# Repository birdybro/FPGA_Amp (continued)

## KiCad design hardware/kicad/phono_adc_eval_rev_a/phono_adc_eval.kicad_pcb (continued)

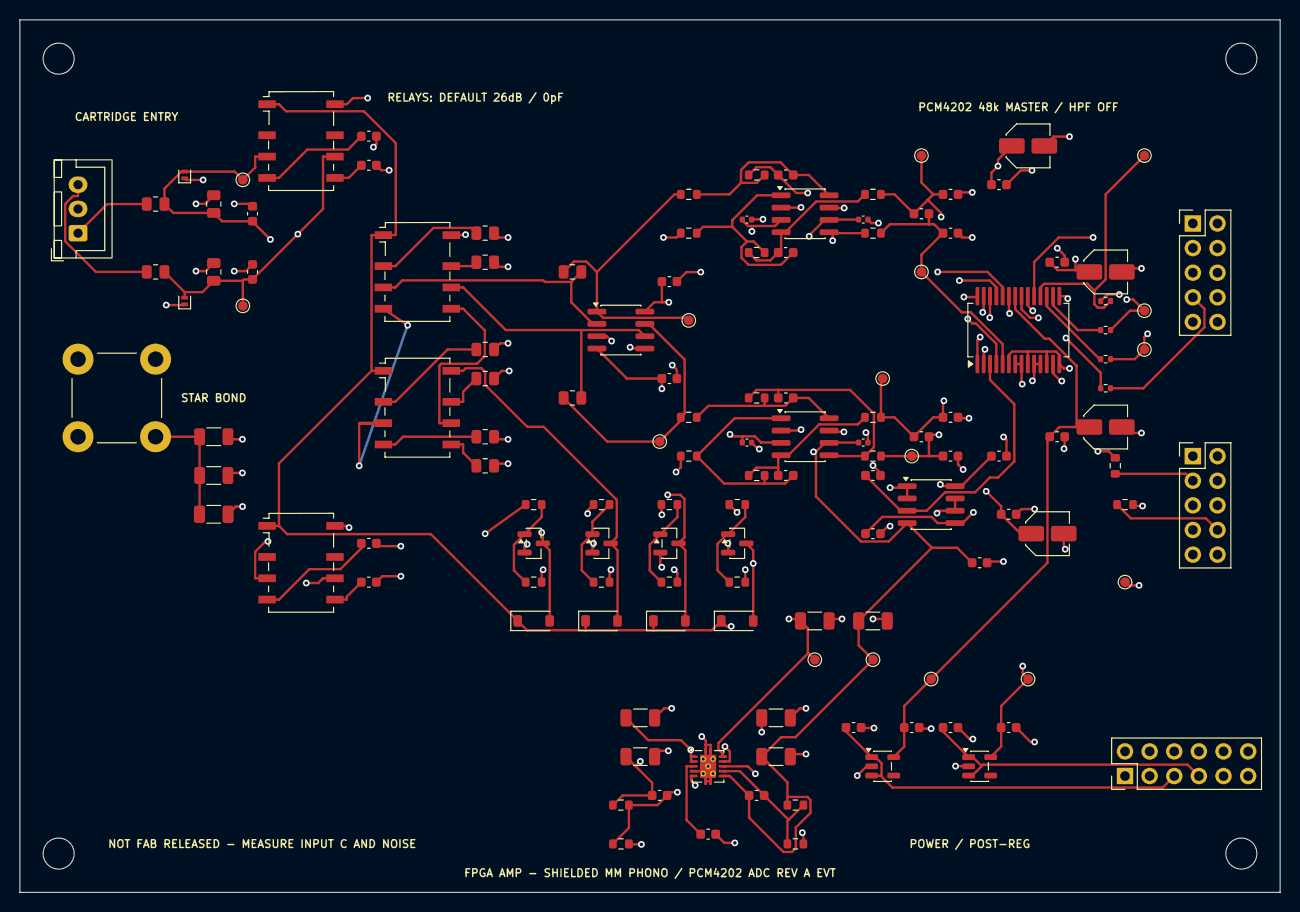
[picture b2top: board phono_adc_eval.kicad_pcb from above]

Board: 4 copper layers, 130.0 x 90.0 mm, 139 parts (0 on the bottom side), 77 nets.

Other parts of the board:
H1, H2, H3, H4: M3_SHIELD_STANDOFF; MountingHole_3.2mm_M3

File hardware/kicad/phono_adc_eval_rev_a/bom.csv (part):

Reference,Value,Footprint,Description
J1,ISOLATED_PANEL_RCA_HARNESS,Connector_JST:JST_XH_B3B-XH-A_1x03_P2.50mm_Vertical,Short shielded harness to enclosure-qualified isolated RCA jacks; connector is EVT only
J2,TURNTABLE_GROUND_POST,TerminalBlock_MetzConnect:TerminalBlock_MetzConnect_360425_1x01_Horizontal_ScrewM4.0_Boxed,EVT screw terminal; production binding post is chassis-mounted
J3,ADC_AUDIO,Connector_PinHeader_2.54mm:PinHeader_2x05_P2.54mm_Vertical,Clock/data harness to digital board; PCM4202 is the 48 kHz I2S master
J4,POWER_INPUT,Connector_PinHeader_2.54mm:PinHeader_2x06_P2.54mm_Vertical,Separately supplied analog; digital; and relay rails from product power board
J5,ADC_CONTROL,Connector_PinHeader_2.54mm:PinHeader_2x05_P2.54mm_Vertical,Low-speed controls; all selection controls default low
U1,TPS7A39DSCR,Package_SON:Texas_DSC0010J_ThermalVias,Dual low-noise post-regulator; ±12 V nominal from separately supplied ±15.5 V
U2,TPS7A2050PDBVR,Package_TO_SOT_SMD:SOT-23-5,Low-noise +5 V ADC analog post-regulator
U3,TPS7A2033PDBVR,Package_TO_SOT_SMD:SOT-23-5,Low-noise +3.3 V ADC digital post-regulator
U4,OPA1656IDR,Package_SO:SOIC-8_3.9x4.9mm_P1.27mm,Dual JFET-input flat gain stage; 2.9 nV/rtHz at 10 kHz; 6 fA/rtHz at 1 kHz
U5,OPA1632DR,Package_SO:SOIC-8_3.9x4.9mm_P1.27mm,Left fully differential PCM4202 driver; enabled by grounding EN with bipolar supplies
U6,OPA1632DR,Package_SO:SOIC-8_3.9x4.9mm_P1.27mm,Right fully differential PCM4202 driver; enabled by grounding EN with bipolar supplies
U7,PCM4202DBR,Package_SO:SSOP-28_5.3x10.2mm_P0.65mm,Stereo 24-bit ADC; 48 kHz master/I2S; 512fS SCKI; internal HPF disabled
U8,OPA1656IDR,Package_SO:SOIC-8_3.9x4.9mm_P1.27mm,Dual voltage follower required because PCM4202 VCOM cannot drive OPA1632 VOCM directly
R1,100R_0.1%,Resistor_SMD:R_0805_2012Metric,
R2,100R_0.1%,Resistor_SMD:R_0805_2012Metric,
R3,47.5k_0.1%_25ppm,Resistor_SMD:R_0805_2012Metric,
R4,47.5k_0.1%_25ppm,Resistor_SMD:R_0805_2012Metric,
D1,PESD5V0X1BCL_EVT,Diode_SMD:D_SOD-882,0.49 pF nominal bidirectional ESD candidate; fit only after leakage/noise review
D2,PESD5V0X1BCL_EVT,Diode_SMD:D_SOD-882,0.49 pF nominal bidirectional ESD candidate; fit only after leakage/noise review
C1,47pF_C0G_1%,Capacitor_SMD:C_0603_1608Metric,
C2,47pF_C0G_1%,Capacitor_SMD:C_0603_1608Metric,
C3,100pF_C0G_1%,Capacitor_SMD:C_0603_1608Metric,
C4,100pF_C0G_1%,Capacitor_SMD:C_0603_1608Metric,
C5,DNP_22pF_C0G_RF,Capacitor_SMD:C_0603_1608Metric,DNP; populate only from RF injection data and include in measured cartridge load
C6,DNP_22pF_C0G_RF,Capacitor_SMD:C_0603_1608Metric,DNP; populate only from RF injection data and include in measured cartridge load
K1,G6K-2F-Y-5V_GAIN_BANK,Relay_SMD:Relay_DPDT_Omron_G6K-2F-Y,Default NC is 26 dB; energized delegates both channels to K2
K2,G6K-2F-Y-5V_GAIN_RANGE,Relay_SMD:Relay_DPDT_Omron_G6K-2F-Y,NC selects 20 dB and NO selects 32 dB only while K1 is energized
K3,G6K-2F-Y-5V_CAP47,Relay_SMD:Relay_DPDT_Omron_G6K-2F-Y,Normally open 47 pF C0G load increment for both channels
K4,G6K-2F-Y-5V_CAP100,Relay_SMD:Relay_DPDT_Omron_G6K-2F-Y,Normally open 100 pF C0G load increment for both channels
R5,19.1k_0.1%,Resistor_SMD:R_0805_2012Metric,
R6,19.1k_0.1%,Resistor_SMD:R_0805_2012Metric,
R7,1.00k_0.1%,Resistor_SMD:R_0805_2012Metric,
R8,1.00k_0.1%,Resistor_SMD:R_0805_2012Metric,
R9,2.12k_0.1%,Resistor_SMD:R_0805_2012Metric,
R10,2.12k_0.1%,Resistor_SMD:R_0805_2012Metric,
R11,492R_0.1%,Resistor_SMD:R_0805_2012Metric,
R12,492R_0.1%,Resistor_SMD:R_0805_2012Metric,
R20,316R_0.1%,Resistor_SMD:R_0603_1608Metric,
R21,316R_0.1%,Resistor_SMD:R_0603_1608Metric,
R22,316R_0.1%,Resistor_SMD:R_0603_1608Metric,
R23,316R_0.1%,Resistor_SMD:R_0603_1608Metric,
C20,1nF_C0G,Capacitor_SMD:C_0603_1608Metric,
C21,1nF_C0G,Capacitor_SMD:C_0603_1608Metric,
R24,40.2R_0.1%,Resistor_SMD:R_0603_1608Metric,
R25,40.2R_0.1%,Resistor_SMD:R_0603_1608Metric,
C22,2.7nF_C0G,Capacitor_SMD:C_0603_1608Metric,
C23,100pF_C0G,Capacitor_SMD:C_0603_1608Metric,
C24,100pF_C0G,Capacitor_SMD:C_0603_1608Metric,
R30,316R_0.1%,Resistor_SMD:R_0603_1608Metric,
R31,316R_0.1%,Resistor_SMD:R_0603_1608Metric,
R32,316R_0.1%,Resistor_SMD:R_0603_1608Metric,
R33,316R_0.1%,Resistor_SMD:R_0603_1608Metric,
C30,1nF_C0G,Capacitor_SMD:C_0603_1608Metric,
C31,1nF_C0G,Capacitor_SMD:C_0603_1608Metric,
R34,40.2R_0.1%,Resistor_SMD:R_0603_1608Metric,
R35,40.2R_0.1%,Resistor_SMD:R_0603_1608Metric,
C32,2.7nF_C0G,Capacitor_SMD:C_0603_1608Metric,
C33,100pF_C0G,Capacitor_SMD:C_0603_1608Metric,
C34,100pF_C0G,Capacitor_SMD:C_0603_1608Metric,
C40,33uF_LOW_ESR,Capacitor_SMD:C_Elec_4x5.8,
C41,100nF_X7R,Capacitor_SMD:C_0603_1608Metric,
C42,33uF_LOW_ESR,Capacitor_SMD:C_Elec_4x5.8,
C43,100nF_X7R,Capacitor_SMD:C_0603_1608Metric,
C44,100nF_X7R,Capacitor_SMD:C_0603_1608Metric,
C45,100nF_X7R,Capacitor_SMD:C_0603_1608Metric,
C46,33uF_LOW_ESR,Capacitor_SMD:C_Elec_4x5.8,
C47,100nF_X7R,Capacitor_SMD:C_0603_1608Metric,
C48,33uF_LOW_ESR,Capacitor_SMD:C_Elec_4x5.8,
C49,100nF_X7R,Capacitor_SMD:C_0603_1608Metric,
R40,22R,Resistor_SMD:R_0402_1005Metric,
R41,33R,Resistor_SMD:R_0402_1005Metric,
R42,33R,Resistor_SMD:R_0402_1005Metric,
R43,33R,Resistor_SMD:R_0402_1005Metric,
R44,100k,Resistor_SMD:R_0603_1608Metric,External control must actively release reset; PCM4202 internal POR remains upstream
R45,10k,Resistor_SMD:R_0603_1608Metric,
Q1,MMBT3904,Package_TO_SOT_SMD:SOT-23,Relay low-side driver
R51,2.2k,Resistor_SMD:R_0603_1608Metric,
R55,100k,Resistor_SMD:R_0603_1608Metric,
D3,1N4148W,Diode_SMD:D_SOD-123,
Q2,MMBT3904,Package_TO_SOT_SMD:SOT-23,Relay low-side driver
R52,2.2k,Resistor_SMD:R_0603_1608Metric,
R56,100k,Resistor_SMD:R_0603_1608Metric,
D4,1N4148W,Diode_SMD:D_SOD-123,
Q3,MMBT3904,Package_TO_SOT_SMD:SOT-23,Relay low-side driver
R53,2.2k,Resistor_SMD:R_0603_1608Metric,
R57,100k,Resistor_SMD:R_0603_1608Metric,
D5,1N4148W,Diode_SMD:D_SOD-123,
Q4,MMBT3904,Package_TO_SOT_SMD:SOT-23,Relay low-side driver
R54,2.2k,Resistor_SMD:R_0603_1608Metric,
R58,100k,Resistor_SMD:R_0603_1608Metric,
D6,1N4148W,Diode_SMD:D_SOD-123,
R60,90.9k_0.1%,Resistor_SMD:R_0603_1608Metric,
R61,10.0k_0.1%,Resistor_SMD:R_0603_1608Metric,
R62,100k_0.1%,Resistor_SMD:R_0603_1608Metric,
R63,10.0k_0.1%,Resistor_SMD:R_0603_1608Metric,
C60,10nF_X7R,Capacitor_SMD:C_0603_1608Metric,
C61,10nF_X7R,Capacitor_SMD:C_0603_1608Metric,
C62,10nF_X7R,Capacitor_SMD:C_0603_1608Metric,
C63,10uF_25V_X7R,Capacitor_SMD:C_1206_3216Metric,
C64,10uF_25V_X7R,Capacitor_SMD:C_1206_3216Metric,
C65,10uF_25V_X7R,Capacitor_SMD:C_1206_3216Metric,
C66,10uF_25V_X7R,Capacitor_SMD:C_1206_3216Metric,
C67,1uF_X7R,Capacitor_SMD:C_0603_1608Metric,
C68,1uF_X7R,Capacitor_SMD:C_0603_1608Metric,
C69,1uF_X7R,Capacitor_SMD:C_0603_1608Metric,
C70,1uF_X7R,Capacitor_SMD:C_0603_1608Metric,
C71,100nF_X7R,Capacitor_SMD:C_0603_1608Metric,
C72,100nF_X7R,Capacitor_SMD:C_0603_1608Metric,
C73,100nF_X7R,Capacitor_SMD:C_0402_1005Metric,
C74,100nF_X7R,Capacitor_SMD:C_0402_1005Metric,
C75,100nF_X7R,Capacitor_SMD:C_0402_1005Metric,
C76,100nF_X7R,Capacitor_SMD:C_0402_1005Metric,
C77,100nF_X7R,Capacitor_SMD:C_0603_1608Metric,
C78,100nF_X7R,Capacitor_SMD:C_0603_1608Metric,
C79,10uF_25V_X7R,Capacitor_SMD:C_1206_3216Metric,
C80,10uF_25V_X7R,Capacitor_SMD:C_1206_3216Metric,
R70,0R_CHASSIS_BOND,Resistor_SMD:R_1206_3216Metric,Reference build bonds signal return to chassis at the cartridge entry
R71,DNP_10R_CHASSIS,Resistor_SMD:R_1206_3216Metric,Alternative only; remove R70 before fitting
C81,DNP_100nF_CHASSIS,Capacitor_SMD:C_1206_3216Metric,Alternative RF bond used only with documented ground strategy
TP1,L_INPUT,TestPoint:TestPoint_Pad_D1.0mm,Local EVT pogo point; do not extend sensitive-node routing
TP2,R_INPUT,TestPoint:TestPoint_Pad_D1.0mm,Local EVT pogo point; do not extend sensitive-node routing
TP3,L_GAIN_OUT,TestPoint:TestPoint_Pad_D1.0mm,Local EVT pogo point; do not extend sensitive-node routing
TP4,R_GAIN_OUT,TestPoint:TestPoint_Pad_D1.0mm,Local EVT pogo point; do not extend sensitive-node routing
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
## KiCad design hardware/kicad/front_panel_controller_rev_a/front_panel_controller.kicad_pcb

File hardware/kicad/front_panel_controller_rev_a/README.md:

# Front-panel controller PCB — revision A EVT

This directory contains the generated, routed KiCad controller board for the
5-inch touchscreen, user controls, and motor-volume daughterboard. Open
`front_panel_controller.kicad_pro` in KiCad 10. KiCad does not live-reload
files changed externally, so close and reopen the schematic/PCB editor after a
generator or routing run.

## Checked artifact

The checked-in board is 150 x 90 mm with six copper layers:

```text
L1  F.Cu    components and signals
L2  GND1    continuous ground reference
L3  PWR     power and routing
L4  SIG2    signals
L5  GND2    continuous ground reference
L6  B.Cu    signals and ground pour
```

KiCad 10.0.5 reports zero schematic ERC violations, zero PCB DRC
violations, and zero unconnected items after zone fill. The open route has
1,827 track segments and 327 vias at minimum 0.20 mm track / 0.30 mm drill.
The source-aware verifier checks the package pin map, connector electrical map,
layer stack, board size, source damping, regulator choice, and routed
geometries.

This is an EVT routing baseline, **not a fabrication release**. In particular,
the checked board deliberately carries `NOT FAB RELEASED` silkscreen and the
following gates remain open:

- print and physically fit the drawing-derived Molex 54104-4031 and 52271-0679
  footprints, obtain assembler DFM review, and inspect first-article joints;
- define the fabricator's six-layer stackup, then review impedance, return
  paths, SDRAM flight time/skew, and LTDC edge integrity;
- perform a specialist layout review of the TPS62132 buck and TPS61165 boost,
  including switch-node copper, hot loops, thermal paths, and emissions;
- freeze enclosure, display, harness, encoder, and mounting geometry; and
- close sourcing, assembly, bring-up, ESD, thermal, EMC, and lifetime tests.

No fabrication-output target is provided while those stop conditions are
open.

## Implemented electrical architecture

- STM32H753ZIT6 in LQFP-144 with all supply pins, 11 local 100 nF bypass
  sites, connected VCAP pins with two 2.2 uF low-ESR capacitors, filtered
  VDDA/VREF+, HSE/LSE footprints, reset, BOOT0, and 10-pin SWD.
- An independently checked 106-I/O allocation covering RGB565 LTDC, touch,
  x16 FMC SDRAM, Quad-SPI, FPGA control SPI, three quadrature encoders,
  mute/standby, ambient sensing, and the motor-volume interface.
- IS42S16160J 32 MiB x16 SDR SDRAM and W25Q256JV 32 MiB Quad-SPI flash.
- Twenty 33 ohm LTDC source-damping resistors plus clock damping for SDRAM and
  Quad-SPI. Values are provisional until stackup-specific measurement/SI.
- Exact NHD-5.0-800480AF-ASXP-CTP electrical pin assignment. Unused RGB LSBs
  are grounded for RGB565; DE, HSYNC, VSYNC, standby, and the capacitive-touch
  reset/interrupt signals are retained.
- Project-local footprints for the exact Molex 54104-4031 40-pin top-contact
  TFT connector and 52271-0679 6-pin bottom-contact touch connector. Their
  manufacturer-drawing pad count, pitch, land size, and fitting-nail geometry
  are locked by `verify.py`; see `footprint_audit.md` for the dimension audit.
- TPS61165 backlight boost from 12 V with a 3.32 ohm feedback resistor for
  approximately 60.2 mA nominal LED current and 32 kHz PWM target. The display
  data sheet's typical LED string voltage is about 21.1 V.
- TPS62132 fixed 3.3 V / 3 A buck. TPS62133 is intentionally rejected here
  because it is the fixed 5 V member, not the 3.3 V part.
- Separate harnesses for panel-mounted encoders/buttons, digital-board control,
  and the motor-volume board. The motor position tracks remain control inputs
  only and never carry audio.
- `FORCE_MUTE_N` defaults asserted through hardware. A healthy MCU must
  intentionally establish control; the GUI is not allowed to become the sole
  safety path.

The high-quality source/model/parameter knobs are panel-mounted optical
encoder candidates rather than PCB-mounted consumer encoders. This keeps shaft
loads in the metal panel and lets enclosure mechanics determine the exact
Grayhill 62H or Bourns EM14 variant. The motorized volume mechanism remains on
the separate, already-routed motor board so its PWM currents do not share the
display/MCU board.

Direct Ethernet is not available in this LQFP-144 Rev-A allocation: the RMII
pin set conflicts with the chosen LTDC/FMC functions. Adding Ethernet requires
an external SPI bridge/module or a package/architecture revision. The eARC
receiver is also intentionally absent; it belongs on the separately licensed
digital/eARC mainboard next to the HDMI connector and ASRC.

## Reproduction

```text
make kicad-controller-generate
make kicad-controller-route FREEROUTING_JAR=/path/to/freerouting.jar
make kicad-controller-check
make kicad-controller-render
```

`generate.py` recreates the native schematic, source placement, custom symbol
library, project, and BOM from one part/net model. It erases routing by design.
`route_open.py` exchanges DSN/SES with Freerouting and refills zones on import.
It also applies one reviewed 1.6 mm U2 ground dogleg when v2.2.4 stops one
connection short; the mandatory DRC remains the acceptance gate. The checked
route used Freerouting v2.2.4. `verify_pin_assignment.py` rejects
duplicate package pins or package-position drift before board generation.

## Primary references

- [Newhaven NHD-5.0-800480AF-ASXP-CTP data sheet](https://newhavendisplay.com/content/specs/NHD-5.0-800480AF-ASXP-CTP.pdf)
- [Molex 54104-4031 product/drawing record](https://www.molex.com/en-us/products/part-detail/541044031)
- [Molex 52271-0679 product/drawing record](https://www.molex.com/en-us/products/part-detail/522710679)
- [ST STM32H753ZI data sheet](https://www.st.com/resource/en/datasheet/stm32h753zi.pdf)
- [ST AN4938 hardware-development guidance](https://www.st.com/resource/en/application_note/an4938-getting-started-with-stm32h74xig-and-stm32h75xig-mcu-hardware-development-stmicroelectronics.pdf)
- [ST official open pin data](https://github.com/STMicroelectronics/STM32_open_pin_data), pinned extract provenance commit `7d1f1514ed5583ec5007ad91236b4e1d377295b1`
- [ISSI IS42S16160J data sheet](https://www.issi.com/WW/pdf/42-45S83200J-16160J.pdf)
- [TI TPS61165 data sheet](https://www.ti.com/lit/ds/symlink/tps61165.pdf)
- [TI TPS62132/TPS6213x data sheet](https://www.ti.com/lit/gpn/TPS62133)
- [Freerouting open autorouter](https://github.com/freerouting/freerouting)

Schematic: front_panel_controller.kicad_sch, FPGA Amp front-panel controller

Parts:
C1: 10uF_25V_X7R; C_1210_3225Metric
C2: 100nF_25V_X7R; C_0603_1608Metric
C3, C4: 22uF_6V3_X7R; C_1210_3225Metric
C5: 3.3nF_X7R; C_0603_1608Metric
C6: 1uF_50V_X7R; C_1206_3216Metric
C7: 220nF_X7R; C_0603_1608Metric
C10, C11, C12, C13, C14, C15, C16, C17, C18, C19, C20, C25, C27, C34, C40, C41, C42, C43, C44, C45, C47: 100nF_X7R; C_0402_1005Metric
C21: 4.7uF_X7R; C_0805_2012Metric
C22, C23: 2.2uF_LOW_ESR; C_0805_2012Metric
C24, C26, C33, C48: 1uF_X7R; C_0603_1608Metric
C28, C29: 12pF_C0G; C_0402_1005Metric
C30, C31: 10pF_C0G_DNP; C_0402_1005Metric
C32: 100nF; C_0603_1608Metric
C46: 10uF_X7R; C_0805_2012Metric
D1: SMBJ15A; D_SMB
D2: MBR0540T1G; D_SOD-123
D3: GREEN_STATUS; LED_0603_1608Metric
F1: 1.5A_PTC; Fuse_1206_3216Metric
FB1, FB2: 600R@100MHz; L_0603_1608Metric_Pad1.05x0.95mm_HandSolder
J1: UI_12V_INPUT; JST_VH_B2P-VH-B_1x02_P3.96mm_Vertical
J2: NHD-5.0-800480AF-ASXP-CTP_TFT; Molex_54104-4031_1x40-2MP_P0.50mm_Horizontal
J3: NHD_CTP_6P; Molex_52271-0679_1x06-2MP_P1.00mm_Horizontal
J4: MOTOR_VOLUME_BOARD; PinHeader_2x06_P2.54mm_Vertical
J5: DIGITAL_BOARD_CONTROL; PinHeader_2x08_P2.54mm_Vertical
J6: PANEL_CONTROLS; PinHeader_2x08_P2.54mm_Vertical
J7: CORTEX_SWD; PinHeader_2x05_P1.27mm_Vertical
JP1: BOOT0; PinHeader_1x02_P2.54mm_Vertical
L1: 2.2uH_4A; L_Bourns_SRN6045TA
L2: 10uH_1A; L_Bourns-SRN4018
R1, R2, R4, R42: 100k; R_0603_1608Metric
R3: 3.32R_1%; R_0805_2012Metric
R10, R11, R12, R13, R14, R15, R16, R17, R18, R19, R20, R21, R22, R23, R24, R25, R26, R27, R28, R29: 33R; R_0402_1005Metric
R30, R31: 22R; R_0402_1005Metric
R40: 0R; R_0402_1005Metric
R41, R45, R46, R47, R48, R49, R50: 10k; R_0603_1608Metric
R43, R44: 2.2k; R_0603_1608Metric
R51: 1k; R_0603_1608Metric
SW1: RESET; Panasonic_EVQPUJ_EVQPUA
TP1: +12V_UI; TestPoint_Plated_Hole_D2.0mm
TP2: +3V3; TestPoint_Plated_Hole_D2.0mm
TP3: GND; TestPoint_Plated_Hole_D2.0mm
TP4: VCAP_CORE; TestPoint_Plated_Hole_D2.0mm
TP5: VDDA; TestPoint_Plated_Hole_D2.0mm
TP6: LCD_LED_A; TestPoint_Plated_Hole_D2.0mm
TP7: BL_FB; TestPoint_Plated_Hole_D2.0mm
TP8: NRST; TestPoint_Plated_Hole_D2.0mm
U1: STM32H753ZIT6; LQFP-144_20x20mm_P0.5mm
U2: IS42S16160J-6TLI_32MiB; TSOP-II-54_22.2x10.16mm_P0.8mm
U3: W25Q256JVSIQ_32MiB; SOIC-8_5.3x5.3mm_P1.27mm
U4: TPS62132RGTR_3V3_3A; VQFN-16-1EP_3x3mm_P0.5mm_EP1.6x1.6mm_ThermalVias
U5: TPS61165DRVR; WSON-6-1EP_2x2mm_P0.65mm_EP1x1.6mm_ThermalVias
Y1: 25MHz_10pF; Crystal_SMD_3225-4Pin_3.2x2.5mm
Y2: 32.768kHz_7pF; Crystal_SMD_3215-2Pin_3.2x1.5mm

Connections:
+3V3: C3.1 (+3V3), C4.1 (+3V3), C10.1 (+3V3), C11.1 (+3V3), C12.1 (+3V3), C13.1 (+3V3), C14.1 (+3V3), C15.1 (+3V3), C16.1 (+3V3), C17.1 (+3V3), C18.1 (+3V3), C19.1 (+3V3), C20.1 (+3V3), C21.1 (+3V3), C40.1 (+3V3), C41.1 (+3V3), C42.1 (+3V3), C43.1 (+3V3), C44.1 (+3V3), C45.1 (+3V3), C46.1 (+3V3), C47.1 (+3V3), C48.1 (+3V3), FB1.1 (+3V3), FB2.1 (+3V3), J2.4 (+3V3), J4.1 (+3V3), J5.1 (+3V3), J6.1 (+3V3), J7.1 (+3V3), JP1.1 (+3V3), L1.2 (+3V3), R2.2 (+3V3), R41.1 (+3V3), R47.1 (+3V3), R49.1 (+3V3), R50.1 (+3V3), TP2.1, U1.6 (+3V3), U1.17 (+3V3), U1.30 (+3V3), U1.39 (+3V3), U1.52 (+3V3), U1.62 (+3V3), U1.72 (+3V3), U1.84 (+3V3), U1.95 (+3V3), U1.108 (+3V3), U1.121 (+3V3), U1.131 (+3V3), U1.143 (+3V3), U1.144 (+3V3), U2.1 (+3V3), U2.3 (+3V3), U2.9 (+3V3), U2.14 (+3V3), U2.27 (+3V3), U2.43 (+3V3), U2.49 (+3V3), U3.8 (+3V3), U4.14 (+3V3)
+3V3_TOUCH: C33.1 (+3V3_TOUCH), C34.1 (+3V3_TOUCH), FB2.2 (+3V3_TOUCH), J3.1 (+3V3_TOUCH), R43.1 (+3V3_TOUCH), R44.1 (+3V3_TOUCH), R45.1 (+3V3_TOUCH), R46.1 (+3V3_TOUCH)
+12V_UI: C1.1 (+12V_UI), C2.1 (+12V_UI), D1.2 (+12V_UI), F1.2 (+12V_UI), L2.1 (+12V_UI), R1.1 (+12V_UI), TP1.1, U4.10 (+12V_UI), U4.11 (+12V_UI), U4.12 (+12V_UI), U5.6 (+12V_UI)
AMBIENT_ADC: J6.14 (AMBIENT_ADC), U1.41 (AMBIENT_ADC)
BACKLIGHT_PWM: R4.1 (BACKLIGHT_PWM), U1.98 (BACKLIGHT_PWM), U5.5 (BACKLIGHT_PWM)
BL_COMP: C7.1 (BL_COMP), U5.2 (BL_COMP)
BL_FB: J2.1 (BL_FB), R3.1 (BL_FB), TP7.1, U5.1 (BL_FB)
BL_SW: D2.1 (BL_SW), L2.2 (BL_SW), U5.4 (BL_SW)
BOOT0: JP1.2 (BOOT0), R42.1 (BOOT0), U1.138 (BOOT0)
BUCK_EN: R1.2 (BUCK_EN), U4.13 (BUCK_EN)
BUCK_PG: R2.1 (BUCK_PG), U4.4 (BUCK_PG)
BUCK_SS: C5.1 (BUCK_SS), U4.9 (BUCK_SS)
BUCK_SW: L1.1 (BUCK_SW), U4.1 (BUCK_SW), U4.2 (BUCK_SW), U4.3 (BUCK_SW)
DB_IRQ_N: J5.7 (DB_IRQ_N), R50.2 (DB_IRQ_N), U1.80 (DB_IRQ_N)
DB_SPI_CS_N: J5.4 (DB_SPI_CS_N), R49.2 (DB_SPI_CS_N), U1.73 (DB_SPI_CS_N)
DB_SPI_MISO: J5.5 (DB_SPI_MISO), U1.75 (DB_SPI_MISO)
DB_SPI_MOSI: J5.6 (DB_SPI_MOSI), U1.76 (DB_SPI_MOSI)
DB_SPI_SCK: J5.3 (DB_SPI_SCK), U1.74 (DB_SPI_SCK)
FORCE_MUTE_N: J5.9 (FORCE_MUTE_N), R48.1 (FORCE_MUTE_N), U1.113 (FORCE_MUTE_N)
GND: C1.2 (GND), C2.2 (GND), C3.2 (GND), C4.2 (GND), C5.2 (GND), C6.2 (GND), C7.2 (GND), C10.2 (GND), C11.2 (GND), C12.2 (GND), C13.2 (GND), C14.2 (GND), C15.2 (GND), C16.2 (GND), C17.2 (GND), C18.2 (GND), C19.2 (GND), C20.2 (GND), C21.2 (GND), C22.2 (GND), C23.2 (GND), C24.2 (GND), C25.2 (GND), C26.2 (GND), C27.2 (GND), C28.2 (GND), C29.2 (GND), C30.2 (GND), C31.2 (GND), C32.2 (GND), C33.2 (GND), C34.2 (GND), C40.2 (GND), C41.2 (GND), C42.2 (GND), C43.2 (GND), C44.2 (GND), C45.2 (GND), C46.2 (GND), C47.2 (GND), C48.2 (GND), D1.1 (GND), D3.1 (GND), J1.2 (GND), J2.3 (GND), J2.5 (GND), J2.6 (GND), J2.7 (GND), J2.13 (GND), J2.14 (GND), J2.21 (GND), J2.22 (GND), J2.23 (GND), J2.29 (GND), J2.36 (GND), J3.2 (GND), J4.2 (GND), J4.11 (GND), J4.12 (GND), J5.2 (GND), J5.10 (GND), J6.2 (GND), J6.15 (GND), J6.16 (GND), J7.3 (GND), J7.5 (GND), J7.9 (GND), R3.2 (GND), R4.2 (GND), R42.2 (GND), R48.2 (GND), SW1.2 (GND), TP3.1, U1.16 (GND), U1.31 (GND), U1.38 (GND), U1.51 (GND), U1.61 (GND), U1.83 (GND), U1.94 (GND), U1.107 (GND), U1.120 (GND), U1.130 (GND), U2.6 (GND), U2.12 (GND), U2.28 (GND), U2.41 (GND), U2.46 (GND), U2.52 (GND), U2.54 (GND), U3.4 (GND), U4.5 (GND), U4.6 (GND), U4.7 (GND), U4.8 (GND), U4.15 (GND), U4.16 (GND), U4.17 (GND), U5.3 (GND), U5.7 (GND), Y1.2 (GND), Y1.4 (GND)
HSE_IN: C28.1 (HSE_IN), U1.23 (HSE_IN), Y1.1 (HSE_IN)
HSE_OUT: C29.1 (HSE_OUT), U1.24 (HSE_OUT), Y1.3 (HSE_OUT)
LCD_B3: J2.24 (LCD_B3), R10.2 (LCD_B3)
LCD_B3_MCU: R10.1 (LCD_B3_MCU), U1.126 (LCD_B3_MCU)
LCD_B4: J2.25 (LCD_B4), R11.2 (LCD_B4)
LCD_B4_MCU: R11.1 (LCD_B4_MCU), U1.127 (LCD_B4_MCU)
LCD_B5: J2.26 (LCD_B5), R12.2 (LCD_B5)
LCD_B5_MCU: R12.1 (LCD_B5_MCU), U1.37 (LCD_B5_MCU)
LCD_B6: J2.27 (LCD_B6), R13.2 (LCD_B6)
LCD_B6_MCU: R13.1 (LCD_B6_MCU), U1.139 (LCD_B6_MCU)
LCD_B7: J2.28 (LCD_B7), R14.2 (LCD_B7)
LCD_B7_MCU: R14.1 (LCD_B7_MCU), U1.140 (LCD_B7_MCU)
LCD_CLK: J2.30 (LCD_CLK), R15.2 (LCD_CLK)
LCD_CLK_MCU: R15.1 (LCD_CLK_MCU), U1.92 (LCD_CLK_MCU)
LCD_DE: J2.34 (LCD_DE), R16.2 (LCD_DE)
LCD_DE_MCU: R16.1 (LCD_DE_MCU), U1.22 (LCD_DE_MCU)
LCD_G2: J2.15 (LCD_G2), R17.2 (LCD_G2)
LCD_G2_MCU: R17.1 (LCD_G2_MCU), U1.42 (LCD_G2_MCU)
LCD_G3: J2.16 (LCD_G3), R18.2 (LCD_G3)
LCD_G3_MCU: R18.1 (LCD_G3_MCU), U1.125 (LCD_G3_MCU)
LCD_G4: J2.17 (LCD_G4), R19.2 (LCD_G4)
LCD_G4_MCU: R19.1 (LCD_G4_MCU), U1.69 (LCD_G4_MCU)
LCD_G5: J2.18 (LCD_G5), R20.2 (LCD_G5)
LCD_G5_MCU: R20.1 (LCD_G5_MCU), U1.70 (LCD_G5_MCU)
LCD_G6: J2.19 (LCD_G6), R21.2 (LCD_G6)
LCD_G6_MCU: R21.1 (LCD_G6_MCU), U1.97 (LCD_G6_MCU)
LCD_G7: J2.20 (LCD_G7), R22.2 (LCD_G7)
LCD_G7_MCU: R22.1 (LCD_G7_MCU), U1.117 (LCD_G7_MCU)
LCD_HSYNC: J2.32 (LCD_HSYNC), R23.2 (LCD_HSYNC)
LCD_HSYNC_MCU: R23.1 (LCD_HSYNC_MCU), U1.96 (LCD_HSYNC_MCU)
LCD_LED_A: C6.1 (LCD_LED_A), D2.2 (LCD_LED_A), J2.2 (LCD_LED_A), TP6.1
LCD_R3: J2.8 (LCD_R3), R24.2 (LCD_R3)
LCD_R3_MCU: R24.1 (LCD_R3_MCU), U1.46 (LCD_R3_MCU)
LCD_R4: J2.9 (LCD_R4), R25.2 (LCD_R4)
LCD_R4_MCU: R25.1 (LCD_R4_MCU), U1.103 (LCD_R4_MCU)
LCD_R5: J2.10 (LCD_R5), R26.2 (LCD_R5)
LCD_R5_MCU: R26.1 (LCD_R5_MCU), U1.101 (LCD_R5_MCU)
LCD_R6: J2.11 (LCD_R6), R27.2 (LCD_R6)
LCD_R6_MCU: R27.1 (LCD_R6_MCU), U1.47 (LCD_R6_MCU)
LCD_R7: J2.12 (LCD_R7), R28.2 (LCD_R7)
LCD_R7_MCU: R28.1 (LCD_R7_MCU), U1.91 (LCD_R7_MCU)
LCD_STBY_N: J2.31 (LCD_STBY_N), U1.1 (LCD_STBY_N)
LCD_VSYNC: J2.33 (LCD_VSYNC), R29.2 (LCD_VSYNC)
LCD_VSYNC_MCU: R29.1 (LCD_VSYNC_MCU), U1.40 (LCD_VSYNC_MCU)
LSE_IN: C30.1 (LSE_IN), U1.8 (LSE_IN), Y2.1 (LSE_IN)
LSE_OUT: C31.1 (LSE_OUT), U1.9 (LSE_OUT), Y2.2 (LSE_OUT)
MODEL_ENC_A: J6.6 (MODEL_ENC_A), U1.134 (MODEL_ENC_A)
MODEL_ENC_B: J6.7 (MODEL_ENC_B), U1.135 (MODEL_ENC_B)
MODEL_PUSH: J6.8 (MODEL_PUSH), U1.128 (MODEL_PUSH)
MOTOR_BOARD_ID: J4.10 (MOTOR_BOARD_ID), U1.27 (MOTOR_BOARD_ID)
MOTOR_CURRENT_ADC: J4.7 (MOTOR_CURRENT_ADC), U1.28 (MOTOR_CURRENT_ADC)
MOTOR_DIR: J4.4 (MOTOR_DIR), U1.118 (MOTOR_DIR)
MOTOR_FAULT_N: J4.6 (MOTOR_FAULT_N), U1.122 (MOTOR_FAULT_N)
MOTOR_PWM: J4.3 (MOTOR_PWM), U1.43 (MOTOR_PWM)
MOTOR_SLEEP: J4.5 (MOTOR_SLEEP), U1.119 (MOTOR_SLEEP)
MUTE_BUTTON: J6.12 (MUTE_BUTTON), U1.111 (MUTE_BUTTON)
NRST: C32.1 (NRST), J7.10 (NRST), R41.2 (NRST), SW1.1 (NRST), TP8.1, U1.25 (NRST)
PARAM_ENC_A: J6.9 (PARAM_ENC_A), U1.81 (PARAM_ENC_A)
PARAM_ENC_B: J6.10 (PARAM_ENC_B), U1.82 (PARAM_ENC_B)
PARAM_PUSH: J6.11 (PARAM_PUSH), U1.129 (PARAM_PUSH)
POT_A_ADC: J4.8 (POT_A_ADC), U1.29 (POT_A_ADC)
POT_B_ADC: J4.9 (POT_B_ADC), U1.36 (POT_B_ADC)
QSPI_CLK: R31.2 (QSPI_CLK), U3.6 (QSPI_CLK)
QSPI_CLK_MCU: R31.1 (QSPI_CLK_MCU), U1.48 (QSPI_CLK_MCU)
QSPI_CS_N: R47.2 (QSPI_CS_N), U1.136 (QSPI_CS_N), U3.1 (QSPI_CS_N)
QSPI_IO0: U1.20 (QSPI_IO0), U3.5 (QSPI_IO0)
QSPI_IO1: U1.21 (QSPI_IO1), U3.2 (QSPI_IO1)
QSPI_IO2: U1.19 (QSPI_IO2), U3.3 (QSPI_IO2)
QSPI_IO3: U1.18 (QSPI_IO3), U3.7 (QSPI_IO3)
SDRAM_A0: U1.10 (SDRAM_A0), U2.23 (SDRAM_A0)
SDRAM_A1: U1.11 (SDRAM_A1), U2.24 (SDRAM_A1)
SDRAM_A2: U1.12 (SDRAM_A2), U2.25 (SDRAM_A2)
SDRAM_A3: U1.13 (SDRAM_A3), U2.26 (SDRAM_A3)
SDRAM_A4: U1.14 (SDRAM_A4), U2.29 (SDRAM_A4)
SDRAM_A5: U1.15 (SDRAM_A5), U2.30 (SDRAM_A5)
SDRAM_A6: U1.50 (SDRAM_A6), U2.31 (SDRAM_A6)
SDRAM_A7: U1.53 (SDRAM_A7), U2.32 (SDRAM_A7)
SDRAM_A8: U1.54 (SDRAM_A8), U2.33 (SDRAM_A8)
SDRAM_A9: U1.55 (SDRAM_A9), U2.34 (SDRAM_A9)
SDRAM_A10: U1.56 (SDRAM_A10), U2.22 (SDRAM_A10)
SDRAM_A11: U1.57 (SDRAM_A11), U2.35 (SDRAM_A11)
SDRAM_A12: U1.87 (SDRAM_A12), U2.19 (SDRAM_A12)
SDRAM_BA0: U1.89 (SDRAM_BA0), U2.20 (SDRAM_BA0)
SDRAM_BA1: U1.90 (SDRAM_BA1), U2.21 (SDRAM_BA1)
SDRAM_CAS_N: U1.132 (SDRAM_CAS_N), U2.38 (SDRAM_CAS_N)
SDRAM_CKE: U1.45 (SDRAM_CKE), U2.18 (SDRAM_CKE)
SDRAM_CLK: R30.2 (SDRAM_CLK), U2.17 (SDRAM_CLK)
SDRAM_CLK_MCU: R30.1 (SDRAM_CLK_MCU), U1.93 (SDRAM_CLK_MCU)
SDRAM_CS_N: U1.44 (SDRAM_CS_N), U2.36 (SDRAM_CS_N)
SDRAM_D0: U1.85 (SDRAM_D0), U2.2 (SDRAM_D0)
SDRAM_D1: U1.86 (SDRAM_D1), U2.4 (SDRAM_D1)
SDRAM_D2: U1.114 (SDRAM_D2), U2.5 (SDRAM_D2)
SDRAM_D3: U1.115 (SDRAM_D3), U2.7 (SDRAM_D3)
SDRAM_D4: U1.58 (SDRAM_D4), U2.8 (SDRAM_D4)
SDRAM_D5: U1.59 (SDRAM_D5), U2.10 (SDRAM_D5)
SDRAM_D6: U1.60 (SDRAM_D6), U2.11 (SDRAM_D6)
SDRAM_D7: U1.63 (SDRAM_D7), U2.13 (SDRAM_D7)
SDRAM_D8: U1.64 (SDRAM_D8), U2.42 (SDRAM_D8)
SDRAM_D9: U1.65 (SDRAM_D9), U2.44 (SDRAM_D9)
SDRAM_D10: U1.66 (SDRAM_D10), U2.45 (SDRAM_D10)
SDRAM_D11: U1.67 (SDRAM_D11), U2.47 (SDRAM_D11)
SDRAM_D12: U1.68 (SDRAM_D12), U2.48 (SDRAM_D12)
SDRAM_D13: U1.77 (SDRAM_D13), U2.50 (SDRAM_D13)
SDRAM_D14: U1.78 (SDRAM_D14), U2.51 (SDRAM_D14)
SDRAM_D15: U1.79 (SDRAM_D15), U2.53 (SDRAM_D15)
SDRAM_LDQM: U1.141 (SDRAM_LDQM), U2.15 (SDRAM_LDQM)
SDRAM_RAS_N: U1.49 (SDRAM_RAS_N), U2.37 (SDRAM_RAS_N)
SDRAM_UDQM: U1.142 (SDRAM_UDQM), U2.16 (SDRAM_UDQM)
SDRAM_WE_N: U1.26 (SDRAM_WE_N), U2.39 (SDRAM_WE_N)
SOURCE_ENC_A: J6.3 (SOURCE_ENC_A), U1.34 (SOURCE_ENC_A)
SOURCE_ENC_B: J6.4 (SOURCE_ENC_B), U1.35 (SOURCE_ENC_B)
SOURCE_PUSH: J6.5 (SOURCE_PUSH), U1.88 (SOURCE_PUSH)
STANDBY_BUTTON: J6.13 (STANDBY_BUTTON), U1.112 (STANDBY_BUTTON)
STATUS_LED: R51.1 (STATUS_LED), U1.2 (STATUS_LED)
STATUS_LED_A: D3.2 (STATUS_LED_A), R51.2 (STATUS_LED_A)
SWCLK: J7.4 (SWCLK), U1.109 (SWCLK)
SWDIO: J7.2 (SWDIO), U1.105 (SWDIO)
SWO: J7.6 (SWO), U1.133 (SWO)
TOUCH_INT_N: J3.5 (TOUCH_INT_N), R45.2 (TOUCH_INT_N), U1.124 (TOUCH_INT_N)
TOUCH_RESET_N: J3.6 (TOUCH_RESET_N), R46.2 (TOUCH_RESET_N), U1.123 (TOUCH_RESET_N)
TOUCH_SCL: J3.3 (TOUCH_SCL), R43.2 (TOUCH_SCL), U1.100 (TOUCH_SCL)
TOUCH_SDA: J3.4 (TOUCH_SDA), R44.2 (TOUCH_SDA), U1.99 (TOUCH_SDA)
UI_12V_IN: F1.1 (UI_12V_IN), J1.1 (UI_12V_IN)
UI_ALIVE: J5.8 (UI_ALIVE), U1.116 (UI_ALIVE)
VCAP_CORE: C22.1 (VCAP_CORE), C23.1 (VCAP_CORE), TP4.1, U1.71 (VCAP_CORE), U1.106 (VCAP_CORE)
VDDA: C24.1 (VDDA), C25.1 (VDDA), FB1.2 (VDDA), R40.1 (VDDA), TP5.1, U1.33 (VDDA)
VREF_PLUS: C26.1 (VREF_PLUS), C27.1 (VREF_PLUS), R40.2 (VREF_PLUS), U1.32 (VREF_PLUS)

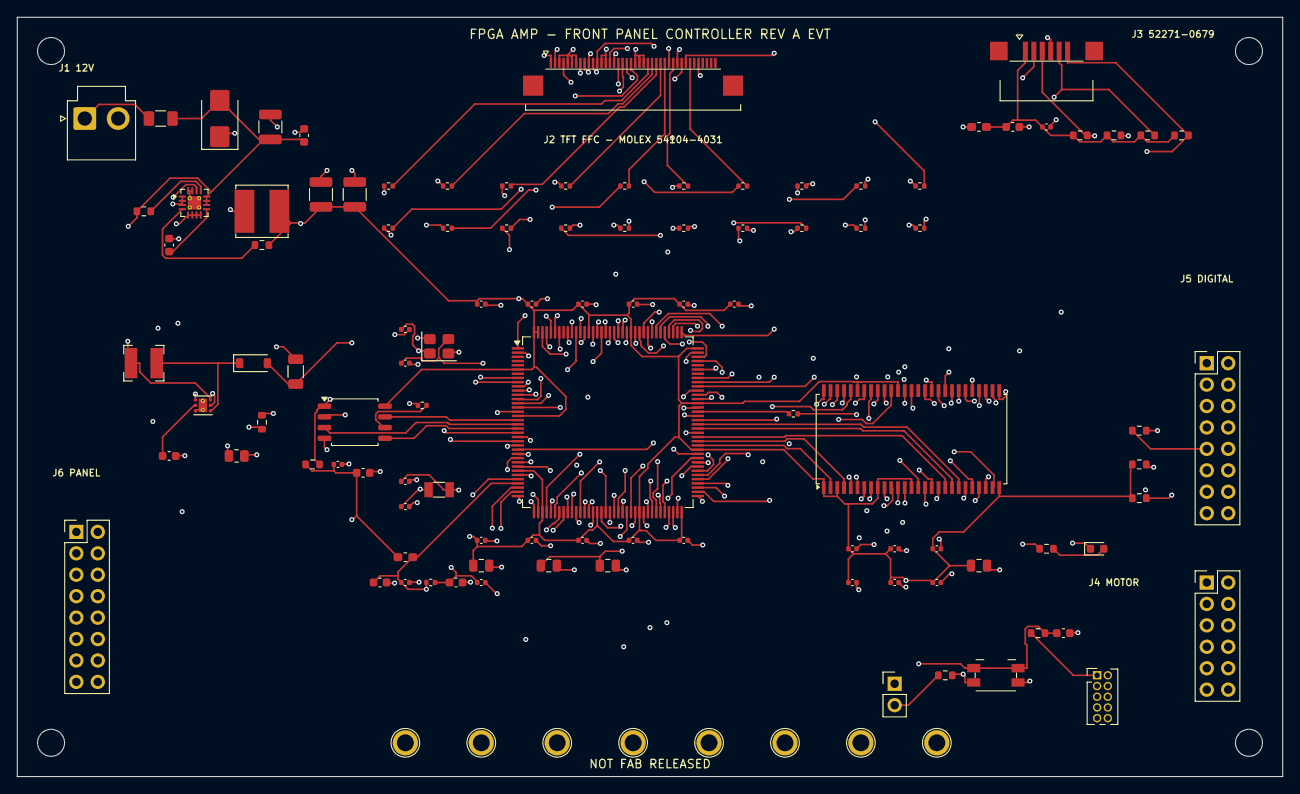
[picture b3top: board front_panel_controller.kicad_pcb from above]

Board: 6 copper layers, 150.0 x 90.0 mm, 115 parts (0 on the bottom side), 147 nets.

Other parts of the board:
H1, H2, H3, H4: M3_CHASSIS; MountingHole_3.2mm_M3

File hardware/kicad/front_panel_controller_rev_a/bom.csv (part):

Reference,Value,Footprint,Description
U1,STM32H753ZIT6,Package_QFP:LQFP-144_20x20mm_P0.5mm,480 MHz UI controller; exact Rev-A pin map in pin_assignment.csv
U2,IS42S16160J-6TLI_32MiB,Package_SO:TSOP-II-54_22.2x10.16mm_P0.8mm,166 MHz x16 SDR SDRAM; 32 MiB framebuffer/work RAM
U3,W25Q256JVSIQ_32MiB,Package_SO:SOIC-8_5.3x5.3mm_P1.27mm,Quad-SPI UI assets and firmware storage
U4,TPS62132RGTR_3V3_3A,Package_DFN_QFN:VQFN-16-1EP_3x3mm_P0.5mm_EP1.6x1.6mm_ThermalVias,Fixed 3.3 V 3 A synchronous buck; TPS62132; not TPS62133
U5,TPS61165DRVR,Package_SON:WSON-6-1EP_2x2mm_P0.65mm_EP1x1.6mm_ThermalVias,38 V boost LED driver; 60 mA nominal current
J1,UI_12V_INPUT,Connector_JST:JST_VH_B2P-VH-B_1x02_P3.96mm_Vertical,Protected 12 V input from product power board
J2,NHD-5.0-800480AF-ASXP-CTP_TFT,fpga_amp:Molex_54104-4031_1x40-2MP_P0.50mm_Horizontal,40-pin 0.5 mm TFT FFC; land pattern from Molex 541041000 rev B
J3,NHD_CTP_6P,fpga_amp:Molex_52271-0679_1x06-2MP_P1.00mm_Horizontal,6-pin 1.0 mm capacitive touch FFC; land pattern from Molex SD-52271-036 rev F
J4,MOTOR_VOLUME_BOARD,Connector_PinHeader_2.54mm:PinHeader_2x06_P2.54mm_Vertical,Harness to isolated motor-volume evaluation board
J5,DIGITAL_BOARD_CONTROL,Connector_PinHeader_2.54mm:PinHeader_2x08_P2.54mm_Vertical,Low-speed control link to FPGA/digital board; no audio samples
J6,PANEL_CONTROLS,Connector_PinHeader_2.54mm:PinHeader_2x08_P2.54mm_Vertical,Panel-mounted optical encoders/buttons and ambient sensor
J7,CORTEX_SWD,Connector_PinHeader_1.27mm:PinHeader_2x05_P1.27mm_Vertical,1.27 mm Cortex debug connector
F1,1.5A_PTC,Fuse:Fuse_1206_3216Metric,Select final hold/trip after measured UI load
D1,SMBJ15A,Diode_SMD:D_SMB,
C1,10uF_25V_X7R,Capacitor_SMD:C_1210_3225Metric,
C2,100nF_25V_X7R,Capacitor_SMD:C_0603_1608Metric,
L1,2.2uH_4A,Inductor_SMD:L_Bourns_SRN6045TA,
C3,22uF_6V3_X7R,Capacitor_SMD:C_1210_3225Metric,
C4,22uF_6V3_X7R,Capacitor_SMD:C_1210_3225Metric,
C5,3.3nF_X7R,Capacitor_SMD:C_0603_1608Metric,
R1,100k,Resistor_SMD:R_0603_1608Metric,
R2,100k,Resistor_SMD:R_0603_1608Metric,
L2,10uH_1A,Inductor_SMD:L_Bourns-SRN4018,
D2,MBR0540T1G,Diode_SMD:D_SOD-123,
C6,1uF_50V_X7R,Capacitor_SMD:C_1206_3216Metric,
R3,3.32R_1%,Resistor_SMD:R_0805_2012Metric,
C7,220nF_X7R,Capacitor_SMD:C_0603_1608Metric,
R4,100k,Resistor_SMD:R_0603_1608Metric,
R10,33R,Resistor_SMD:R_0402_1005Metric,LTDC source damping; verify by scope/SI
R11,33R,Resistor_SMD:R_0402_1005Metric,LTDC source damping; verify by scope/SI
R12,33R,Resistor_SMD:R_0402_1005Metric,LTDC source damping; verify by scope/SI
R13,33R,Resistor_SMD:R_0402_1005Metric,LTDC source damping; verify by scope/SI
R14,33R,Resistor_SMD:R_0402_1005Metric,LTDC source damping; verify by scope/SI
R15,33R,Resistor_SMD:R_0402_1005Metric,LTDC source damping; verify by scope/SI
R16,33R,Resistor_SMD:R_0402_1005Metric,LTDC source damping; verify by scope/SI
R17,33R,Resistor_SMD:R_0402_1005Metric,LTDC source damping; verify by scope/SI
R18,33R,Resistor_SMD:R_0402_1005Metric,LTDC source damping; verify by scope/SI
R19,33R,Resistor_SMD:R_0402_1005Metric,LTDC source damping; verify by scope/SI
R20,33R,Resistor_SMD:R_0402_1005Metric,LTDC source damping; verify by scope/SI
R21,33R,Resistor_SMD:R_0402_1005Metric,LTDC source damping; verify by scope/SI
R22,33R,Resistor_SMD:R_0402_1005Metric,LTDC source damping; verify by scope/SI
R23,33R,Resistor_SMD:R_0402_1005Metric,LTDC source damping; verify by scope/SI
R24,33R,Resistor_SMD:R_0402_1005Metric,LTDC source damping; verify by scope/SI
R25,33R,Resistor_SMD:R_0402_1005Metric,LTDC source damping; verify by scope/SI
R26,33R,Resistor_SMD:R_0402_1005Metric,LTDC source damping; verify by scope/SI
R27,33R,Resistor_SMD:R_0402_1005Metric,LTDC source damping; verify by scope/SI
R28,33R,Resistor_SMD:R_0402_1005Metric,LTDC source damping; verify by scope/SI
R29,33R,Resistor_SMD:R_0402_1005Metric,LTDC source damping; verify by scope/SI
R30,22R,Resistor_SMD:R_0402_1005Metric,SDRAM clock source termination
R31,22R,Resistor_SMD:R_0402_1005Metric,QSPI clock source termination
C10,100nF_X7R,Capacitor_SMD:C_0402_1005Metric,One per STM32 VDD/VDD33_USB pin; place at assigned power pin
C11,100nF_X7R,Capacitor_SMD:C_0402_1005Metric,One per STM32 VDD/VDD33_USB pin; place at assigned power pin
C12,100nF_X7R,Capacitor_SMD:C_0402_1005Metric,One per STM32 VDD/VDD33_USB pin; place at assigned power pin
C13,100nF_X7R,Capacitor_SMD:C_0402_1005Metric,One per STM32 VDD/VDD33_USB pin; place at assigned power pin
C14,100nF_X7R,Capacitor_SMD:C_0402_1005Metric,One per STM32 VDD/VDD33_USB pin; place at assigned power pin
C15,100nF_X7R,Capacitor_SMD:C_0402_1005Metric,One per STM32 VDD/VDD33_USB pin; place at assigned power pin
C16,100nF_X7R,Capacitor_SMD:C_0402_1005Metric,One per STM32 VDD/VDD33_USB pin; place at assigned power pin
C17,100nF_X7R,Capacitor_SMD:C_0402_1005Metric,One per STM32 VDD/VDD33_USB pin; place at assigned power pin
C18,100nF_X7R,Capacitor_SMD:C_0402_1005Metric,One per STM32 VDD/VDD33_USB pin; place at assigned power pin
C19,100nF_X7R,Capacitor_SMD:C_0402_1005Metric,One per STM32 VDD/VDD33_USB pin; place at assigned power pin
C20,100nF_X7R,Capacitor_SMD:C_0402_1005Metric,One per STM32 VDD/VDD33_USB pin; place at assigned power pin
C21,4.7uF_X7R,Capacitor_SMD:C_0805_2012Metric,
C22,2.2uF_LOW_ESR,Capacitor_SMD:C_0805_2012Metric,VCAP; two capacitors total; VCAP pins connected per ST AN4938
C23,2.2uF_LOW_ESR,Capacitor_SMD:C_0805_2012Metric,
FB1,600R@100MHz,Inductor_SMD:L_0603_1608Metric_Pad1.05x0.95mm_HandSolder,
C24,1uF_X7R,Capacitor_SMD:C_0603_1608Metric,
C25,100nF_X7R,Capacitor_SMD:C_0402_1005Metric,
R40,0R,Resistor_SMD:R_0402_1005Metric,
C26,1uF_X7R,Capacitor_SMD:C_0603_1608Metric,
C27,100nF_X7R,Capacitor_SMD:C_0402_1005Metric,
Y1,25MHz_10pF,Crystal:Crystal_SMD_3225-4Pin_3.2x2.5mm,
Y2,32.768kHz_7pF,Crystal:Crystal_SMD_3215-2Pin_3.2x1.5mm,
C28,12pF_C0G,Capacitor_SMD:C_0402_1005Metric,
C29,12pF_C0G,Capacitor_SMD:C_0402_1005Metric,
C30,10pF_C0G_DNP,Capacitor_SMD:C_0402_1005Metric,DNP pending crystal CL calculation
C31,10pF_C0G_DNP,Capacitor_SMD:C_0402_1005Metric,DNP pending crystal CL calculation
R41,10k,Resistor_SMD:R_0603_1608Metric,
C32,100nF,Capacitor_SMD:C_0603_1608Metric,
SW1,RESET,Button_Switch_SMD:Panasonic_EVQPUJ_EVQPUA,
R42,100k,Resistor_SMD:R_0603_1608Metric,
JP1,BOOT0,Connector_PinHeader_2.54mm:PinHeader_1x02_P2.54mm_Vertical,
FB2,600R@100MHz,Inductor_SMD:L_0603_1608Metric_Pad1.05x0.95mm_HandSolder,
C33,1uF_X7R,Capacitor_SMD:C_0603_1608Metric,
C34,100nF_X7R,Capacitor_SMD:C_0402_1005Metric,
R43,2.2k,Resistor_SMD:R_0603_1608Metric,
R44,2.2k,Resistor_SMD:R_0603_1608Metric,
R45,10k,Resistor_SMD:R_0603_1608Metric,
R46,10k,Resistor_SMD:R_0603_1608Metric,
C40,100nF_X7R,Capacitor_SMD:C_0402_1005Metric,SDRAM VDD/VDDQ bypass
C41,100nF_X7R,Capacitor_SMD:C_0402_1005Metric,SDRAM VDD/VDDQ bypass
C42,100nF_X7R,Capacitor_SMD:C_0402_1005Metric,SDRAM VDD/VDDQ bypass
C43,100nF_X7R,Capacitor_SMD:C_0402_1005Metric,SDRAM VDD/VDDQ bypass
C44,100nF_X7R,Capacitor_SMD:C_0402_1005Metric,SDRAM VDD/VDDQ bypass
C45,100nF_X7R,Capacitor_SMD:C_0402_1005Metric,SDRAM VDD/VDDQ bypass
C46,10uF_X7R,Capacitor_SMD:C_0805_2012Metric,
C47,100nF_X7R,Capacitor_SMD:C_0402_1005Metric,
C48,1uF_X7R,Capacitor_SMD:C_0603_1608Metric,
R47,10k,Resistor_SMD:R_0603_1608Metric,
R48,10k,Resistor_SMD:R_0603_1608Metric,Default asserted; firmware must release mute intentionally
R49,10k,Resistor_SMD:R_0603_1608Metric,
R50,10k,Resistor_SMD:R_0603_1608Metric,
R51,1k,Resistor_SMD:R_0603_1608Metric,
D3,GREEN_STATUS,LED_SMD:LED_0603_1608Metric,
TP1,+12V_UI,TestPoint:TestPoint_Plated_Hole_D2.0mm,EVT bring-up test point
TP2,+3V3,TestPoint:TestPoint_Plated_Hole_D2.0mm,EVT bring-up test point
TP3,GND,TestPoint:TestPoint_Plated_Hole_D2.0mm,EVT bring-up test point
TP4,VCAP_CORE,TestPoint:TestPoint_Plated_Hole_D2.0mm,EVT bring-up test point
TP5,VDDA,TestPoint:TestPoint_Plated_Hole_D2.0mm,EVT bring-up test point
TP6,LCD_LED_A,TestPoint:TestPoint_Plated_Hole_D2.0mm,EVT bring-up test point
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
